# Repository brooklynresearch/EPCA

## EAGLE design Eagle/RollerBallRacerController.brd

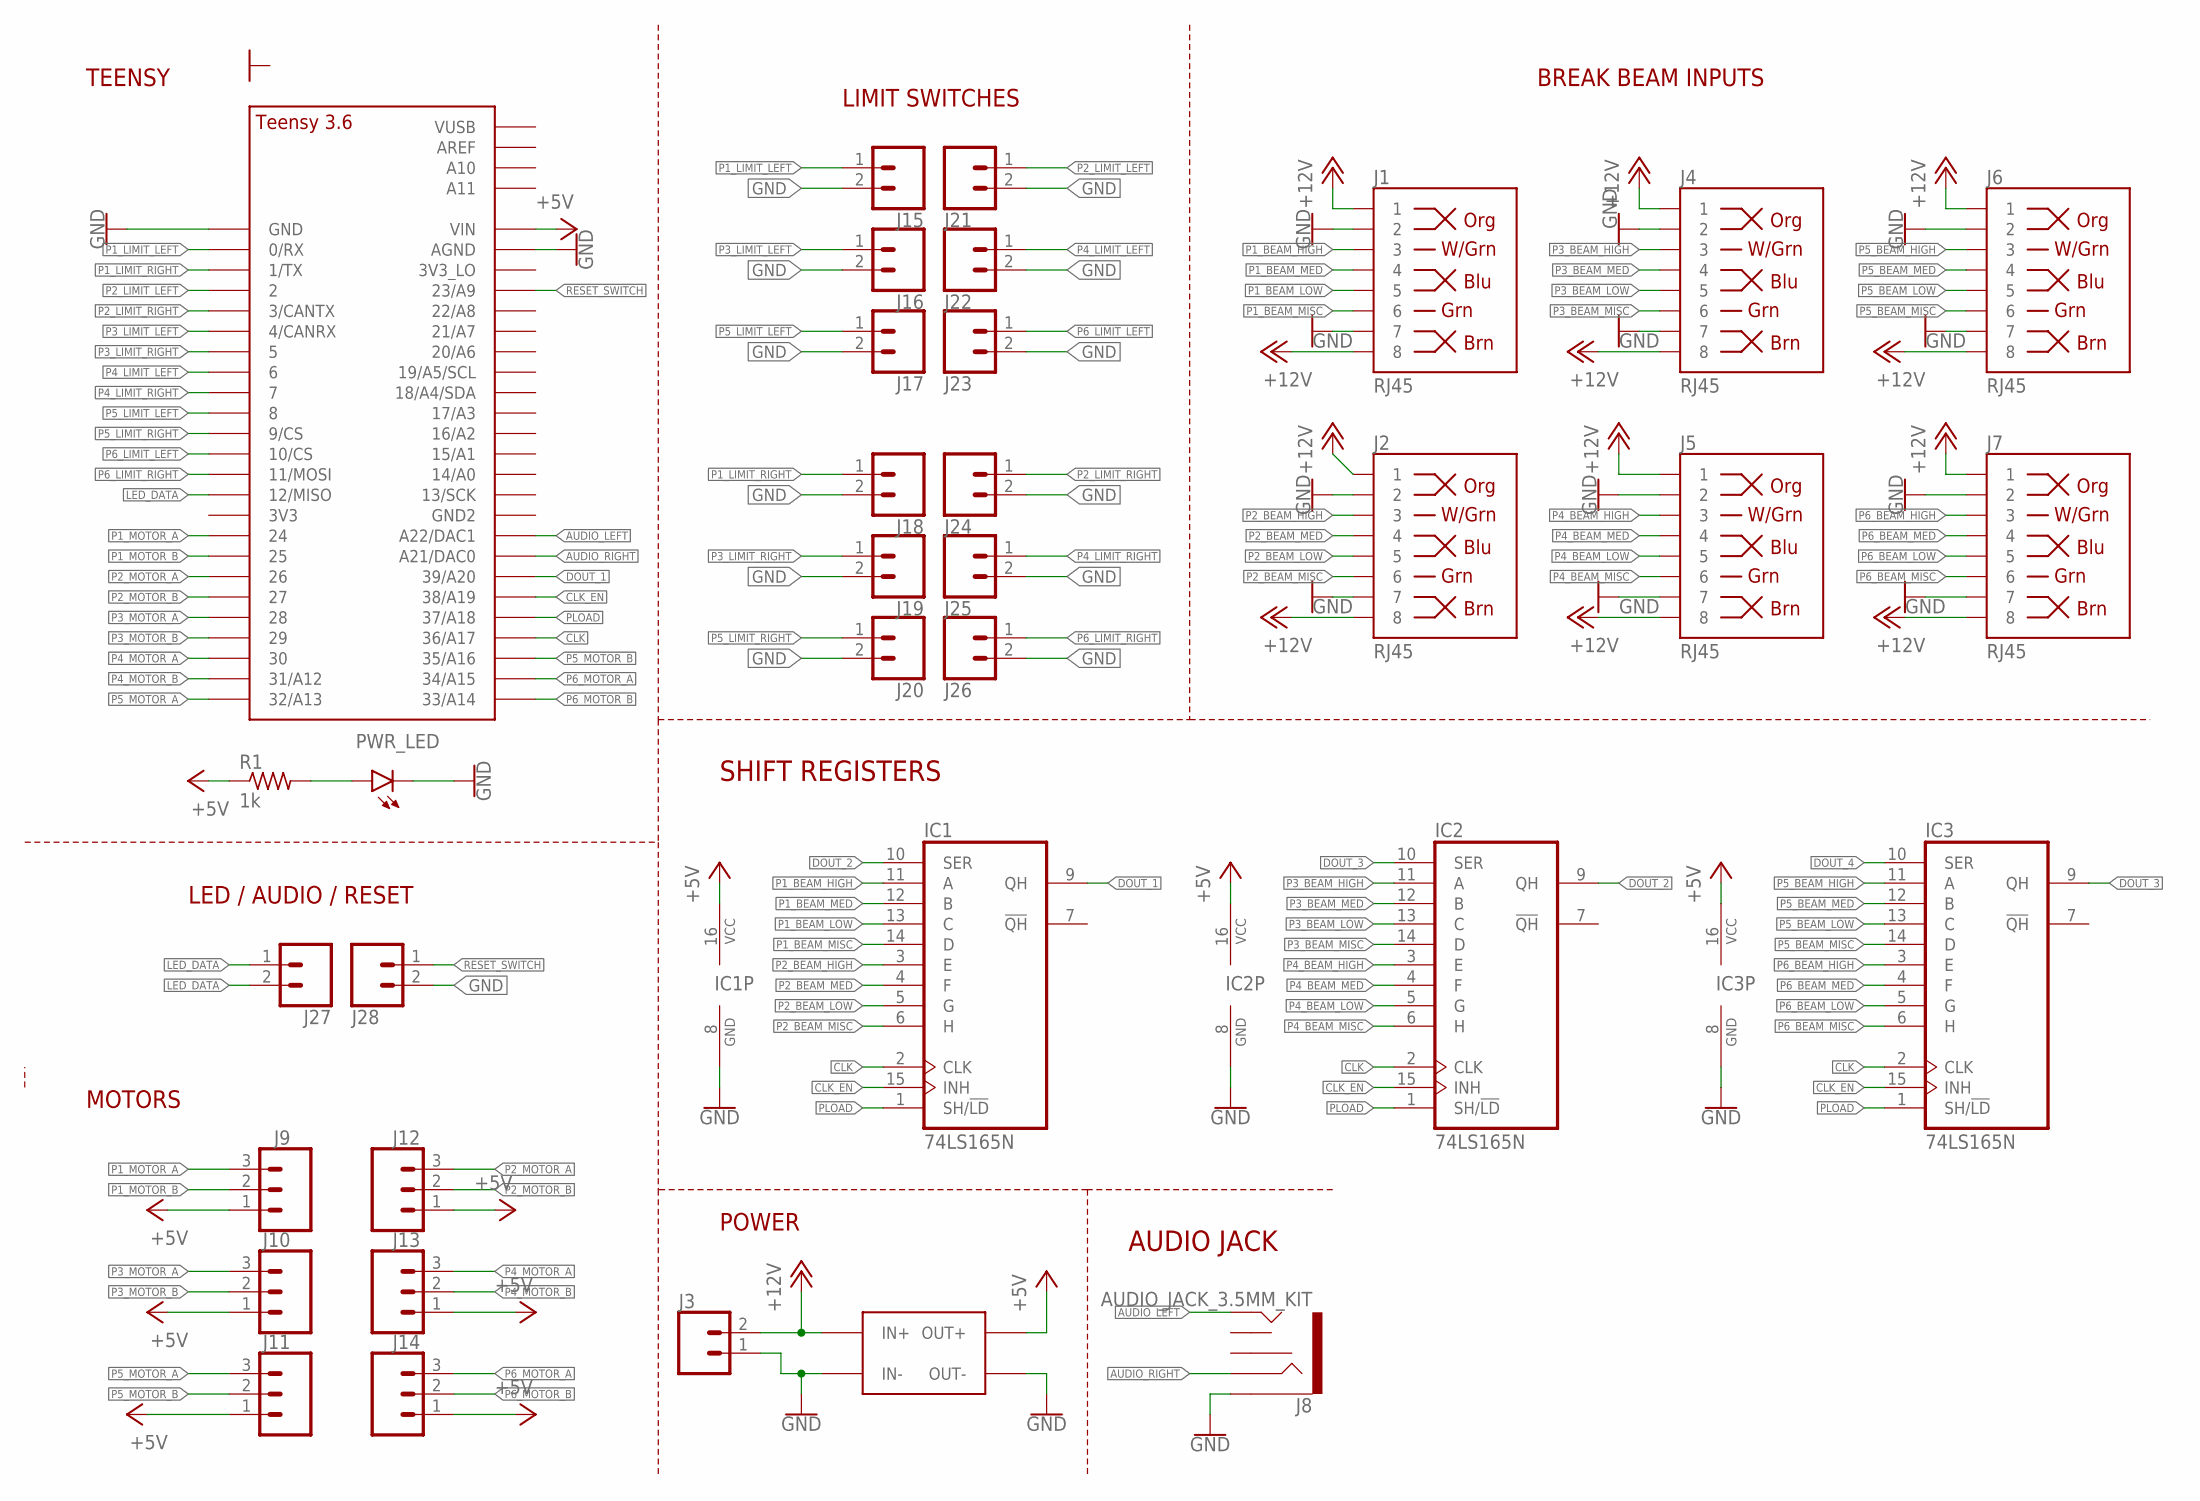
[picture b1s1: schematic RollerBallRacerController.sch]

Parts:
IC1, IC2, IC3: 74LS165N; DIL16
J1, J2, J4, J5, J6, J7: RJ45; RJ45-8
J3: CONN_025MM; SCREWTERMINAL-5MM-2
J8: AUDIO_JACK_3.5MM_KIT; AUDIO-JACK-KIT
J9, J10, J11, J12, J13, J14: CONN_03POLAR; MOLEX-1X3
J15, J16, J17, J18, J19, J20, J21, J22, J23, J24, J25, J26, J27, J28: CONN_02POLAR; MOLEX-1X2
PWR_LED: LED5MM
R1: 1k; 0204/7
U$2: LM2956_DC_DC; LM2596
U$3: TEENSY_3.5/3.6_BASIC

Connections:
+5V: IC1.16 (VCC), IC2.16 (VCC), IC3.16 (VCC), J9.1, J10.1, J11.1, J12.1, J13.1, J14.1, R1.1, U$2.P$4 (OUT+), U$3.VIN
+12V: J1.1, J1.8, J2.1, J2.8, J3.2, J4.1, J4.8, J5.1, J5.8, J6.1, J6.8, J7.1, J7.8, U$2.P$1 (IN+)
AUDIO_LEFT: J8.TIP, U$3.A22/DAC1
AUDIO_RIGHT: J8.RING, U$3.21/DAC0 (A21/DAC0)
CLK: IC1.2 (CLK), IC2.2 (CLK), IC3.2 (CLK), U$3.36/A17
CLK_EN: IC1.15 (INH), IC2.15 (INH), IC3.15 (INH), U$3.38/A19
DOUT_1: IC1.9 (QH), U$3.39/A20
DOUT_2: IC1.10 (SER), IC2.9 (QH)
DOUT_3: IC2.10 (SER), IC3.9 (QH)
DOUT_4: IC3.10 (SER)
GND: IC1.8 (GND), IC2.8 (GND), IC3.8 (GND), J1.2, J1.7, J2.2, J2.7, J3.1, J4.2, J4.7, J5.2, J5.7, J6.2, J6.7, J7.2, J7.7, J8.SLEEVE, J15.2, J16.2, J17.2, J18.2, J19.2, J20.2, J21.2, J22.2, J23.2, J24.2, J25.2, J26.2, J28.2, PWR_LED.K (C), U$2.P$2 (IN-), U$2.P$3 (OUT-), U$3.AGND, U$3.GND
LED_DATA: J27.1, J27.2, U$3.12/MISO
unnamed: PWR_LED.A, R1.2
P1_BEAM_HIGH: IC1.11 (A), J1.3
P1_BEAM_LOW: IC1.13 (C), J1.5
P1_BEAM_MED: IC1.12 (B), J1.4
P1_BEAM_MISC: IC1.14 (D), J1.6
P1_LIMIT_LEFT: J15.1, U$3.0/RX
P1_LIMIT_RIGHT: J18.1, U$3.1/TX
P1_MOTOR_A: J9.3, U$3.24
P1_MOTOR_B: J9.2, U$3.25
P2_BEAM_HIGH: IC1.3 (E), J2.3
P2_BEAM_LOW: IC1.5 (G), J2.5
P2_BEAM_MED: IC1.4 (F), J2.4
P2_BEAM_MISC: IC1.6 (H), J2.6
P2_LIMIT_LEFT: J21.1, U$3.2
P2_LIMIT_RIGHT: J24.1, U$3.3/CANTX
P2_MOTOR_A: J12.3, U$3.26
P2_MOTOR_B: J12.2, U$3.27
P3_BEAM_HIGH: IC2.11 (A), J4.3
P3_BEAM_LOW: IC2.13 (C), J4.5
P3_BEAM_MED: IC2.12 (B), J4.4
P3_BEAM_MISC: IC2.14 (D), J4.6
P3_LIMIT_LEFT: J16.1, U$3.4/CANRX
P3_LIMIT_RIGHT: J19.1, U$3.5
P3_MOTOR_A: J10.3, U$3.28
P3_MOTOR_B: J10.2, U$3.29
P4_BEAM_HIGH: IC2.3 (E), J5.3
P4_BEAM_LOW: IC2.5 (G), J5.5
P4_BEAM_MED: IC2.4 (F), J5.4
P4_BEAM_MISC: IC2.6 (H), J5.6
P4_LIMIT_LEFT: J22.1, U$3.6
P4_LIMIT_RIGHT: J25.1, U$3.7
P4_MOTOR_A: J13.3, U$3.30
P4_MOTOR_B: J13.2, U$3.31/A12
P5_BEAM_HIGH: IC3.11 (A), J6.3
P5_BEAM_LOW: IC3.13 (C), J6.5
P5_BEAM_MED: IC3.12 (B), J6.4
P5_BEAM_MISC: IC3.14 (D), J6.6
P5_LIMIT_LEFT: J17.1, U$3.8
P5_LIMIT_RIGHT: J20.1, U$3.9/CS
P5_MOTOR_A: J11.3, U$3.32/A13
P5_MOTOR_B: J11.2, U$3.35/A16
P6_BEAM_HIGH: IC3.3 (E), J7.3
P6_BEAM_LOW: IC3.5 (G), J7.5
P6_BEAM_MED: IC3.4 (F), J7.4
P6_BEAM_MISC: IC3.6 (H), J7.6
P6_LIMIT_LEFT: J23.1, U$3.10/CS
P6_LIMIT_RIGHT: J26.1, U$3.11/MOSI
P6_MOTOR_A: J14.3, U$3.34/A15
P6_MOTOR_B: J14.2, U$3.33/A14
PLOAD: IC1.1 (SH/!LD), IC2.1 (SH/!LD), IC3.1 (SH/!LD), U$3.37/A18
RESET_SWITCH: J28.1, U$3.23/A9

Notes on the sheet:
LIMIT SWITCHES
BREAK BEAM INPUTS
LED / AUDIO / RESET
POWER
MOTORS
TEENSY
AUDIO JACK
SHIFT REGISTERS

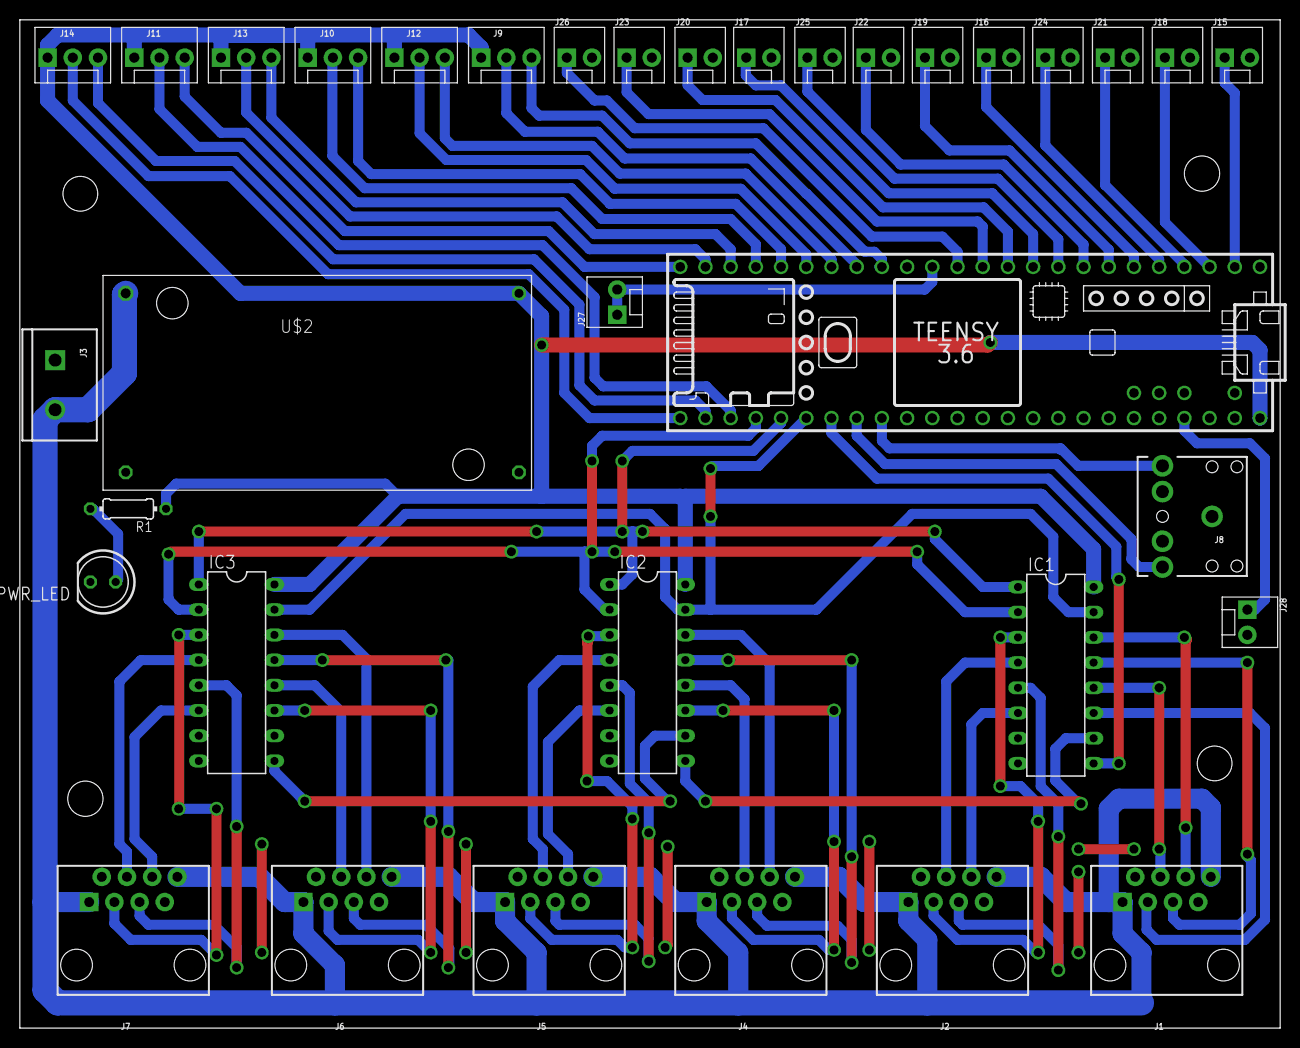
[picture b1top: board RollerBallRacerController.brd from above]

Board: 2 copper layers, 127.0 x 101.6 mm, 35 parts (0 on the bottom side), 62 nets.

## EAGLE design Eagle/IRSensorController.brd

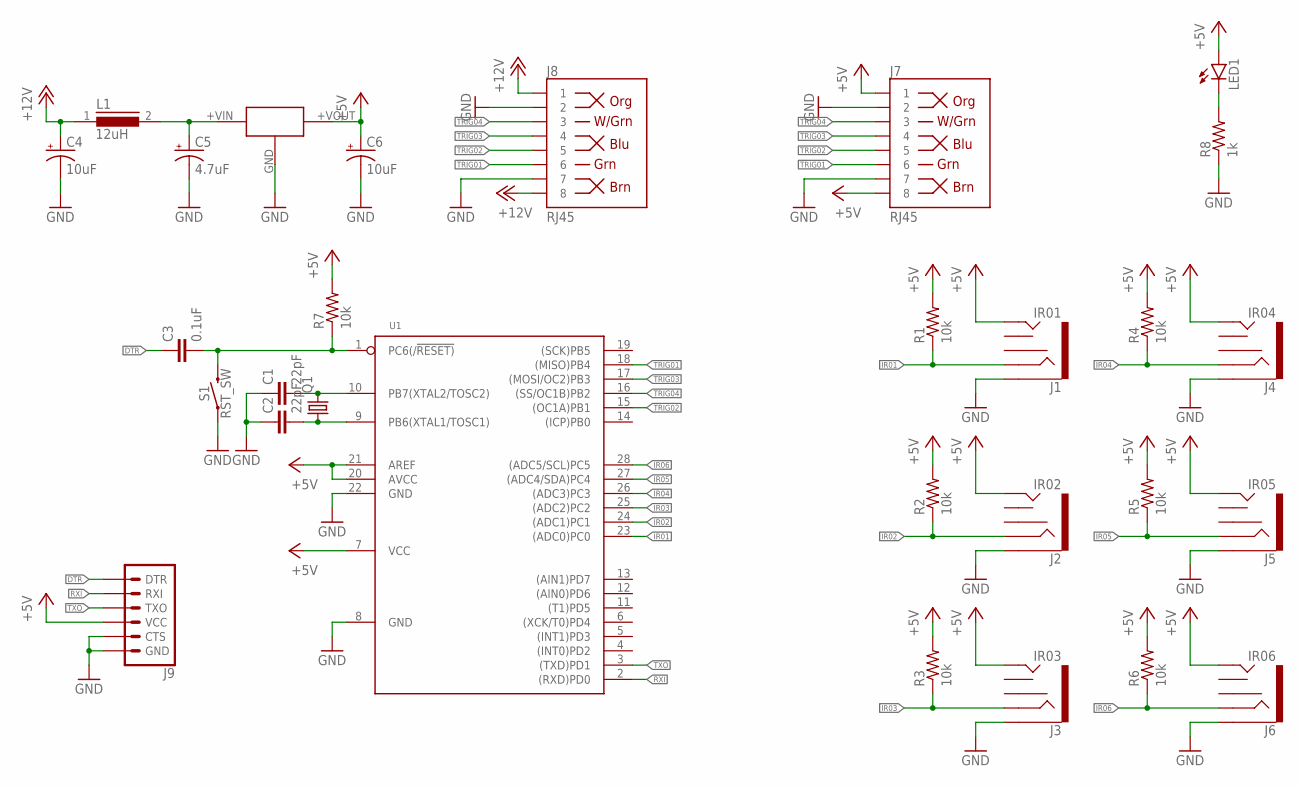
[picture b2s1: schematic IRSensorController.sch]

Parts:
C1, C2: 22pF; C050-025X075
C3: 0.1uF; C050-025X075
C4, C6: 10uF; E3,5-8
C5: 4.7uF; E2,5-7
J1: IR01; AUDIO-JACK-KIT
J2: IR02; AUDIO-JACK-KIT
J3: IR03; AUDIO-JACK-KIT
J4: IR04; AUDIO-JACK-KIT
J5: IR05; AUDIO-JACK-KIT
J6: IR06; AUDIO-JACK-KIT
J7, J8: RJ45; RJ45-8
J9: 6_PIN_SERIAL_TARGETSILK; 6_PIN_SERIAL_TARGET_SIDE_W_SILK
L1: 12uH; SUKW1-17
LED1: LED5MM
Q1: CRYSTALHC49S; HC49/S
R1, R2, R3, R4, R5, R6, R7: 10k; 0204/7
R8: 1k; 0204/7
S1: RST_SW; TACTILE_SWITCH_PTH_6.0MM
U1: MCU-ATMEGA328P-PU(DIP28); DIP28-2.54-34.7X7.62MM
U$1: R_78E_5V; R_78E

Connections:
+5V: C6.+, J1.TIP, J2.TIP, J3.TIP, J4.TIP, J5.TIP, J6.TIP, J7.1, J7.8, J9.P$4 (VCC), LED1.A, R1.2, R2.2, R3.2, R4.2, R5.2, R6.2, R7.2, U1.7 (VCC), U1.20 (AVCC), U1.21 (AREF), U$1.+VOUT
+12V: C4.+, J8.1, J8.8, L1.1
DTR: C3.1, J9.P$1 (DTR)
GND: C1.1, C2.1, C4.-, C5.-, C6.-, J1.SLEEVE, J2.SLEEVE, J3.SLEEVE, J4.SLEEVE, J5.SLEEVE, J6.SLEEVE, J7.2, J7.7, J8.2, J8.7, J9.P$5 (CTS), J9.P$6 (GND), R8.1, S1.1, U1.8 (GND), U1.22 (GND), U$1.GND
IR01: J1.RING, R1.1, U1.23 ((ADC0)PC0)
IR02: J2.RING, R2.1, U1.24 ((ADC1)PC1)
IR03: J3.RING, R3.1, U1.25 ((ADC2)PC2)
IR04: J4.RING, R4.1, U1.26 ((ADC3)PC3)
IR05: J5.RING, R5.1, U1.27 ((ADC4/SDA)PC4)
IR06: J6.RING, R6.1, U1.28 ((ADC5/SCL)PC5)
unnamed: C5.+, L1.2, U$1.+VIN
unnamed: LED1.K (C), R8.2
unnamed: C2.2, Q1.1, U1.9 (PB6(XTAL1/TOSC1))
unnamed: C1.2, Q1.2, U1.10 (PB7(XTAL2/TOSC2))
unnamed: C3.2, R7.1, S1.3 (2), U1.1 (PC6(/!RESET))
RXI: J9.P$3 (RXI), U1.2 ((RXD)PD0)
TRIG01: J7.6, J8.6, U1.18 ((MISO)PB4)
TRIG02: J7.5, J8.5, U1.15 ((OC1A)PB1)
TRIG03: J7.4, J8.4, U1.17 ((MOSI/OC2)PB3)
TRIG04: J7.3, J8.3, U1.16 ((SS/OC1B)PB2)
TXO: J9.P$2 (TXO), U1.3 ((TXD)PD1)

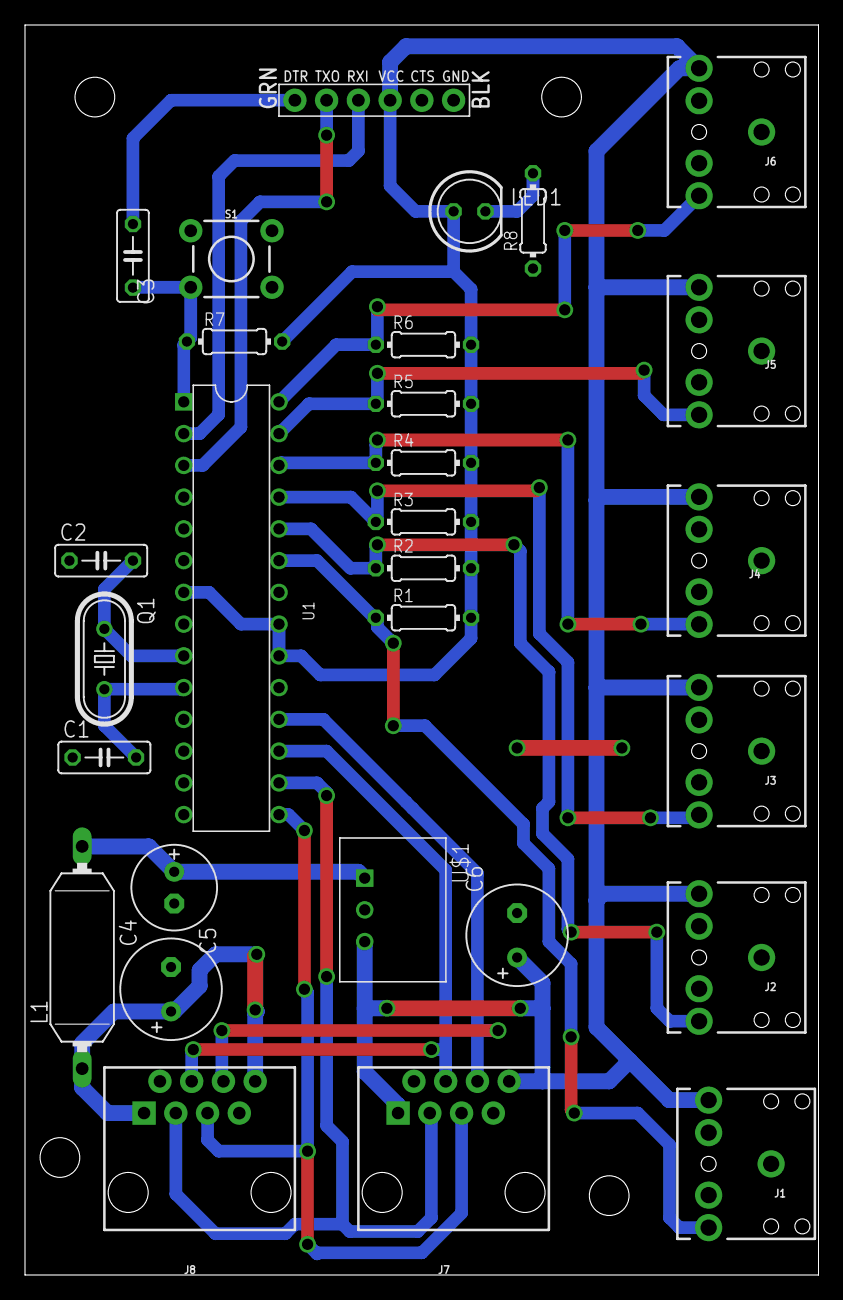
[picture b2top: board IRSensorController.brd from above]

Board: 2 copper layers, 63.5 x 100.0 mm, 29 parts (0 on the bottom side), 21 nets.

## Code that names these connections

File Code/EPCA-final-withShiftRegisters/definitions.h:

// players
const uint8_t numPlayers = 6;
const uint8_t numSensors = numPlayers * 3;

// switch pins
#define  RESET_PIN  23

#define  P1_LIMIT_LEFT  0
#define  P1_LIMIT_RIGHT  1
#define  P2_LIMIT_LEFT  2
#define  P2_LIMIT_RIGHT  3
#define  P3_LIMIT_LEFT  4
#define  P3_LIMIT_RIGHT  5
#define  P4_LIMIT_LEFT  6
#define  P4_LIMIT_RIGHT  7
#define  P5_LIMIT_LEFT  8
#define  P5_LIMIT_RIGHT  9
#define  P6_LIMIT_LEFT  10
#define  P6_LIMIT_RIGHT  11

// LED pins
#define  LED_PIN  12
#define  NUM_LEDS  14

/*  motor pins

    Driving DC motors with L293N, using 2 pins instead of 3
      Enable pin: always +5v
      InA: digital, HIGH = forward / LOW = backward
      InB: analog, 0-255 / 255-0 depending on InA is HIGH / LOW

*/
#define P1_MOTOR_DIR_A 24
#define P1_MOTOR_DIR_B 25
#define P2_MOTOR_DIR_A 26
#define P2_MOTOR_DIR_B 27
#define P3_MOTOR_DIR_A 28
#define P3_MOTOR_DIR_B 29
#define P4_MOTOR_DIR_A 30
#define P4_MOTOR_DIR_B 31
#define P5_MOTOR_DIR_A 32
#define P5_MOTOR_DIR_B 35
#define P6_MOTOR_DIR_A 34
#define P6_MOTOR_DIR_B 33

/*  player input pins, top to bottom:

        100  100  100
           50   50
             25

*/

#define NUMBER_OF_SHIFT_CHIPS   3
#define DATA_WIDTH   NUMBER_OF_SHIFT_CHIPS * 8

#define LOAD_PIN    37
#define ENABLE_PIN  38
#define DATA_PIN    39
#define CLOCK_PIN   36

unsigned long SENSOR_VALUES;
unsigned long OLD_SENSOR_VALUES;

bool motorTriggerValue[24];
uint8_t motorLookUp[24] = {4,4,4,4,5,5,5,5,2,2,2,2,3,3,3,3,0,0,0,0,1,1,1,1};
uint8_t multiplierLookUp[24] = {0,2,3,1,0,2,3,1,0,2,3,1,0,2,3,1,0,2,3,1,0,2,3,1};

uint8_t limitSwitchesLeft[numPlayers] = {
  P1_LIMIT_LEFT,
  P2_LIMIT_LEFT,
  P3_LIMIT_LEFT,
  P4_LIMIT_LEFT,
  P5_LIMIT_LEFT,
  P6_LIMIT_LEFT
};

uint8_t limitSwitchesRight[numPlayers] = {
  P1_LIMIT_RIGHT,
  P2_LIMIT_RIGHT,
  P3_LIMIT_RIGHT,
  P4_LIMIT_RIGHT,
  P5_LIMIT_RIGHT,
  P6_LIMIT_RIGHT
};


// motor arrays
byte motorDirectionA[numPlayers] = {
  P1_MOTOR_DIR_A,
  P2_MOTOR_DIR_A,
  P3_MOTOR_DIR_A,
  P4_MOTOR_DIR_A,
  P5_MOTOR_DIR_A,
  P6_MOTOR_DIR_A
};

byte motorDirectionB[numPlayers] = {
  P1_MOTOR_DIR_B,
  P2_MOTOR_DIR_B,
  P3_MOTOR_DIR_B,
  P4_MOTOR_DIR_B,
  P5_MOTOR_DIR_B,
  P6_MOTOR_DIR_B
};

float motorPosition[numPlayers] = {
  0, 0, 0, 0, 0, 0
};

bool motorMoving[numPlayers] = {
  false, false, false, false, false, false
};

unsigned long startMillis[numPlayers] = {
  0, 0, 0, 0, 0, 0
};

float playerMovementPeriod[numPlayers] = {
  0, 0, 0, 0, 0, 0
};

// skee ball sensor value arrays
uint8_t currentVal[numSensors];
uint8_t previousVal[numSensors];

// de-bounced button objects

Bounce resetButton = Bounce(RESET_PIN, 50);

Bounce p1LimitLeft = Bounce(P1_LIMIT_LEFT, 50);
Bounce p2LimitLeft = Bounce(P2_LIMIT_LEFT, 50);
Bounce p3LimitLeft = Bounce(P3_LIMIT_LEFT, 50);
Bounce p4LimitLeft = Bounce(P4_LIMIT_LEFT, 50);
Bounce p5LimitLeft = Bounce(P5_LIMIT_LEFT, 50);
Bounce p6LimitLeft = Bounce(P6_LIMIT_LEFT, 50);

Bounce p1LimitRight = Bounce(P1_LIMIT_RIGHT, 50);
Bounce p2LimitRight = Bounce(P2_LIMIT_RIGHT, 50);
Bounce p3LimitRight = Bounce(P3_LIMIT_RIGHT, 50);
Bounce p4LimitRight = Bounce(P4_LIMIT_RIGHT, 50);
Bounce p5LimitRight = Bounce(P5_LIMIT_RIGHT, 50);
Bounce p6LimitRight = Bounce(P6_LIMIT_RIGHT, 50);

// arays for buttons
Bounce leftLimits[numPlayers] = {
  p1LimitLeft,
  p2LimitLeft,
  p3LimitLeft,
  p4LimitLeft,
  p5LimitLeft,
  p6LimitLeft
};

Bounce rightLimits[numPlayers] = {
  p1LimitRight,
  p2LimitRight,
  p3LimitRight,
  p4LimitRight,
  p5LimitRight,
  p6LimitRight
};

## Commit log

2019-08-29 added prototype
2019-08-31 separated definitions, fix timing code
2019-09-01 added ball and win sounds
2019-09-03 Added LED code, cycle through win sounds
2019-09-03 Added limit switch bracket model
2019-09-03 Fixed bracket sides
2019-09-08 motors running on 2 pin config, 3 sensors per player, updated 3D models
2019-09-11 Added 1 line debug mode, updated motor timings, updated 3D models
2019-09-12 fixed light code, updated 3D models
2019-09-16 Updated celebrity mount w/ magnets, changed light code for WS2815
2019-09-24 Added eagle files, final code
2019-09-25 Fixed limit switch pinout
2019-09-25 fixed folder structure, updated pins
2019-09-26 update traces on PCBs
2019-10-17 Mechanical Sensor Board and Code
    All new code and board designs for the mechanical sensors. These include the IR Controller, the Main Controller, and the new code associated with both. Plus the basic mount design for the Main Contro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

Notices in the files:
parts and their libraries:
SparkFun-Connectors: Licensing: Creative Commons ShareAlike 4.0 International - https://creativecommons.org/licenses/by-sa/4.0
